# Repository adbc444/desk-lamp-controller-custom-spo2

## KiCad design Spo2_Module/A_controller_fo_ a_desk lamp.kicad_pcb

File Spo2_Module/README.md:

# Desk Lamp Controller PCB (Arduino Nano)

A compact printed circuit board (PCB) design for a desk lamp controller, regulating 5V LEDs, powered by an Arduino Nano v3.x microcontroller board.

---

## 🛠 Technical Specifications

* **Main Controller:** Arduino Nano v3.x
* **Load/Output:** 5V LED regulation
* **Inputs/Controls:** Push buttons / Custom input logic
* **EDA Tool:** KiCad

---

## 📁 Repository Structure

```text
.
├── 3dAndOther/                             # 3D STEP model for mechanical CAD (.step)
├── spo2_stuffYT.pretty/                    # Custom project footprint library
├── A_controller_fo_a_desk lamp.kicad_pcb   # PCB layout and routing
├── A_controller_fo_a_desk lamp.kicad_pro   # Main KiCad project file
├── A_controller_fo_a_desk lamp.kicad_sch   # Schematic diagram
├── TrainingYTWSPO2Staff.kicad_sym          # Custom project symbol library
├── fp-lib-table                            # Footprint library table for custom dependencies
├── gerbers.zip                             # Ready-to-manufacture Gerber and Drill files
├── .gitignore                              # Git ignore rules for KiCad temp files
└── README.md                               # Project documentation

------------------------------------------------------------------------------------------------------------------------------------------------------------------------------------------------------------------------------

🚀 Getting Started
1. Opening the Project in KiCad
To open this project with all custom symbols and footprints properly linked:

Clone this repository or download it as a ZIP archive.

Open the A_controller_fo_a_desk lamp.kicad_pro file in KiCad.

All custom symbols (TrainingYTWSPO2Staff.kicad_sym) and footprints (spo2_stuffYT.pretty) will load automatically via the local fp-lib-table.

2. Manufacturing (JLCPCB, PCBWay, etc.)
All necessary fabrication files are bundled in the gerbers.zip archive. Simply upload this ZIP file directly to your preferred PCB manufacturer's website.

3. Enclosure Design
The 3dAndOther/ directory contains a 3D model of the populated board in .step format. It is ready to be imported into SolidWorks, Fusion 360, or FreeCAD for designing a custom desk lamp enclosure.

👨‍💻 Author
Nazar Hryshko

Student at Wrocław University of Science and Technology (Politechnika Wrocławska)

📄 License
This project is distributed under the CERN Open Hardware Licence Version 2 - Permissive (CERN-OHL-P). You are free to redistribute and modify this hardware design.

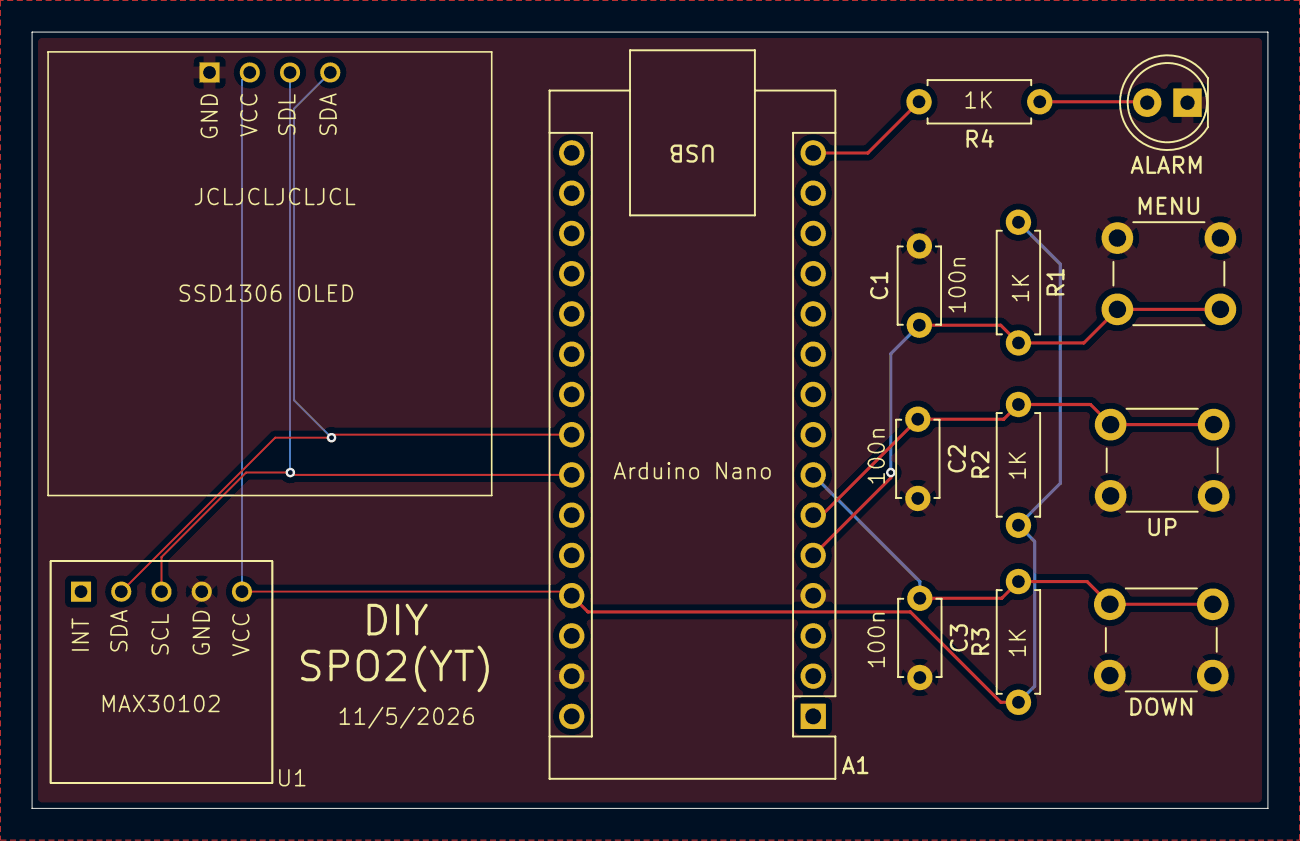
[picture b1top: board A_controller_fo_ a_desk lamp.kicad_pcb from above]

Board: 4 copper layers, 78.0 x 49.0 mm, 14 parts (0 on the bottom side), 9 nets.

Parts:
A1: Arduino_Nano_v3.x; Arduino_Nano
ALARM: LED; LED_D5.0mm
C1, C2, C3: 100n; C_Disc_D4.7mm_W2.5mm_P5.00mm
DOWN: SW_Push; SW_PUSH_6mm
MENU: SW_Push; SW_PUSH_6mm
R1, R2, R3, R4: 1k; R_Axial_DIN0207_L6.3mm_D2.5mm_P7.62mm_Horizontal
U1: MAX30102; MAX30102_MODULEYT
U2: SSD1306
UP: SW_Push; SW_PUSH_6mm

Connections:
+5V: A1.27 (+5V), R1.1, R2.1, R3.1, U1.5 (VCC), U2.2 (VCC)
GND: A1.4 (GND), A1.29 (GND), ALARM.1 (K), C1.2, C2.2, C3.2, DOWN.1, MENU.1, U1.4 (GND), U2.1 (GND), UP.1
unnamed: A1.23 (A4), U1.2 (SDA), U2.4 (SDA)
unnamed: A1.24 (A5), U1.3 (SCL), U2.3 (SCL)
unnamed: A1.5 (D2), C1.1, MENU.2, R1.2
unnamed: A1.6 (D3), C2.1, R2.2, UP.2
unnamed: A1.7 (D4), C3.1, DOWN.2, R3.2
unnamed: A1.15 (D12), R4.2
unnamed: ALARM.2 (A), R4.1
